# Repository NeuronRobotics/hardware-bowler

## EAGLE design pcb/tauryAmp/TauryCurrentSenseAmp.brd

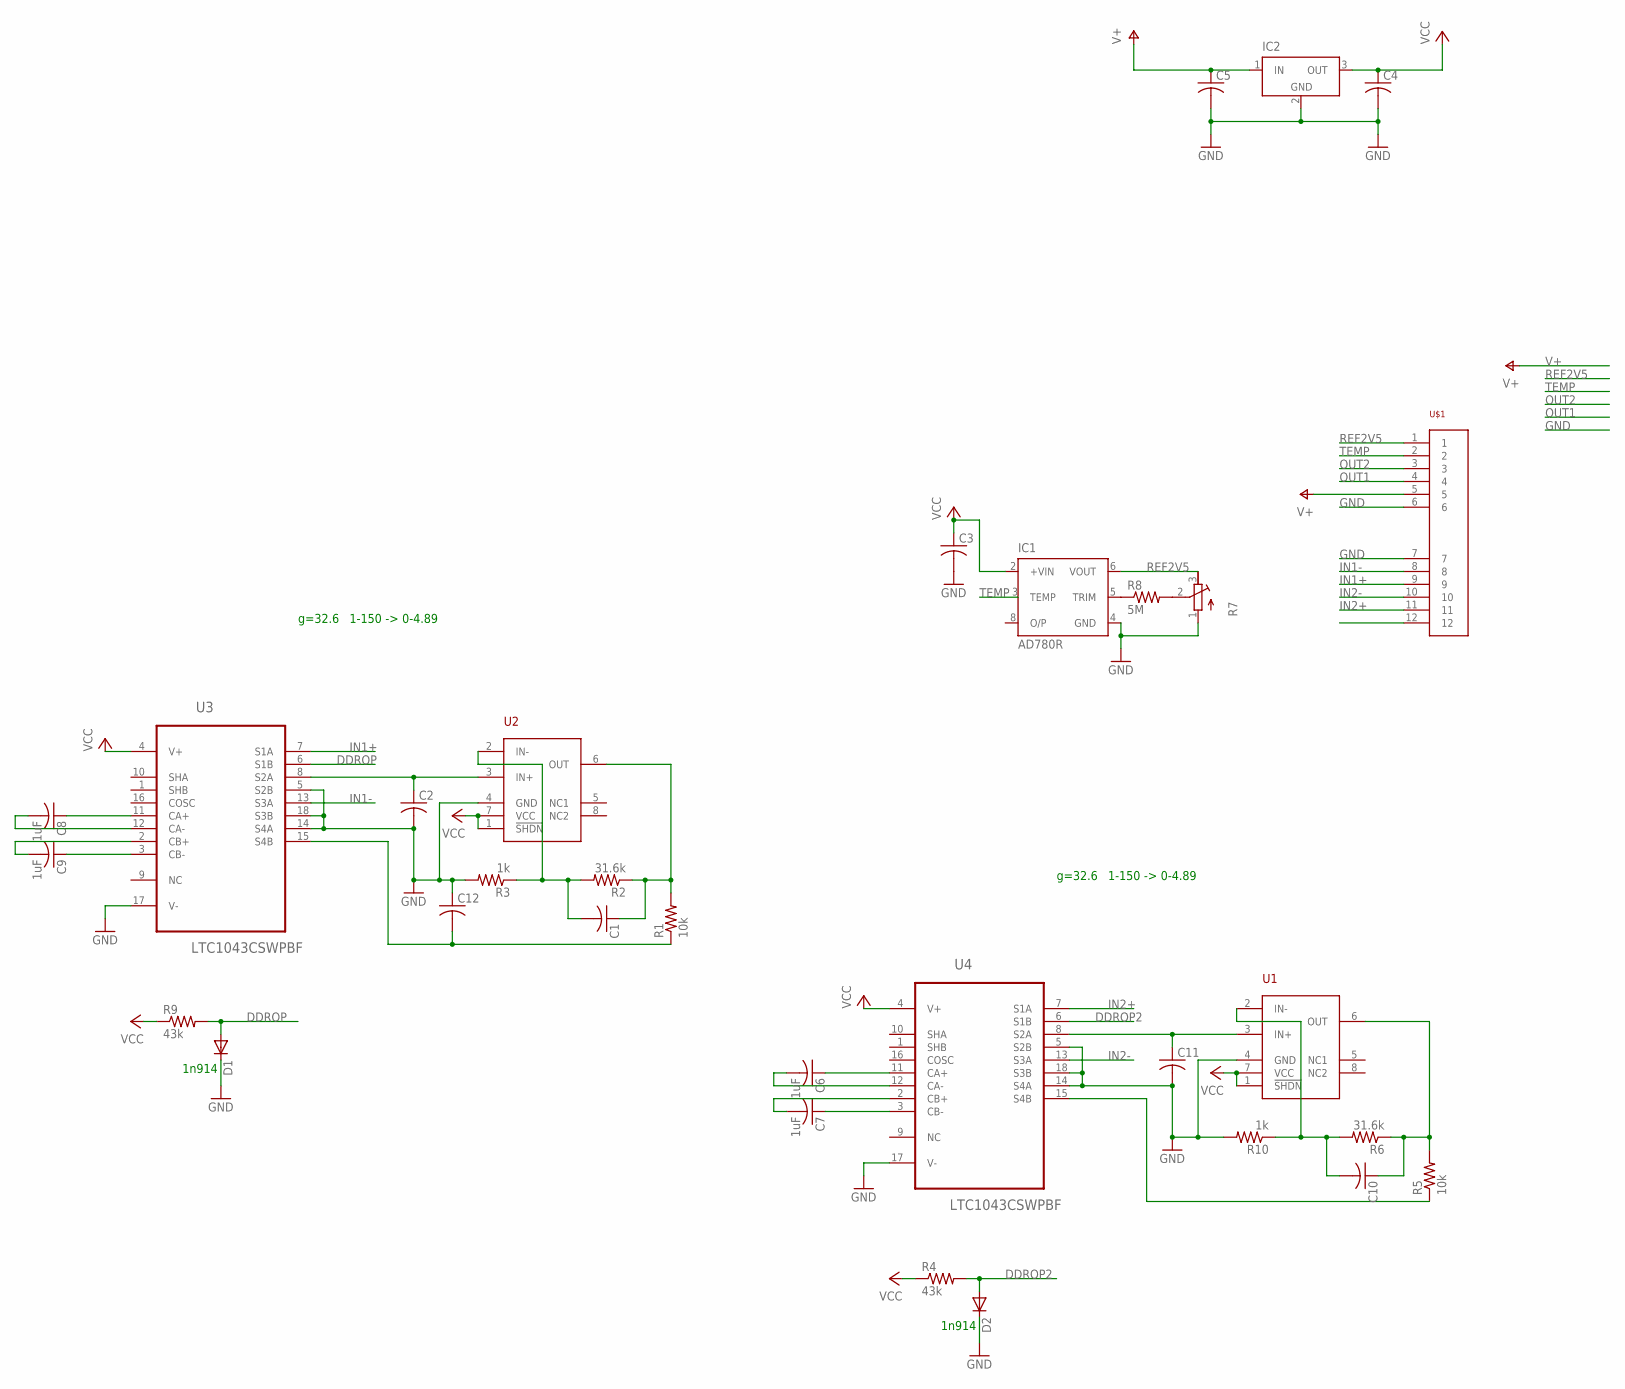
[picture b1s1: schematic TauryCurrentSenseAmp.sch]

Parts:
C1, C2, C3, C4, C5, C10, C11, C12: C-USC0805; C0805
C6, C7, C8, C9: 1uF; C0805
D1: DIODE-SOD323-R; SOD323-R
D2: DIODE-SOD523; SOD523
IC1: AD780R; SO8
IC2: LT1129CST5; SOT223
R1, R5: 10k; R0805
R2, R6: 31.6k; R0805
R3, R10: 1k; R0805
R4, R9: 43k; R0805
R7: R-TRIMM5W; RTRIM5W
R8: 5M; R0805
U1, U2: MAX4239; SO8
U3, U4: LTC1043CSWPBF; SOIC127P1032X264-18N
U$1: DMB-4770; DMB-4770-PCB

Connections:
DDROP: D1.A, R9.2, U3.6 (S1B)
DDROP2: D2.A, R4.2, U4.6 (S1B)
GND: C2.2, C3.2, C4.2, C5.2, C11.2, C12.1, D1.C, D2.C, IC1.4 (GND), IC2.2 (GND), IC2.4 (GND), R3.2, R7.1 (A), R10.2, U1.4 (GND), U2.4 (GND), U3.5 (S2B), U3.14 (S4A), U3.17 (V-), U3.18 (S3B), U4.5 (S2B), U4.14 (S4A), U4.17 (V-), U4.18 (S3B), U$1.6, U$1.7
IN1+: U3.7 (S1A), U$1.9
IN1-: U3.13 (S3A), U$1.8
IN2+: U4.7 (S1A), U$1.11
IN2-: U4.13 (S3A), U$1.10
unnamed: C2.1, U2.3 (IN+), U3.8 (S2A)
unnamed: C12.2, R1.1, U3.15 (S4B)
unnamed: C6.1, U4.11 (CA+)
unnamed: C1.2, R2.2, R3.1, U2.2 (IN-)
unnamed: IC1.5 (TRIM), R8.1
unnamed: R7.2 (S), R8.2
unnamed: C8.1, U3.11 (CA+)
unnamed: C8.2, U3.12 (CA-)
unnamed: C9.2, U3.2 (CB+)
unnamed: C9.1, U3.3 (CB-)
unnamed: C6.2, U4.12 (CA-)
unnamed: C7.2, U4.2 (CB+)
unnamed: C7.1, U4.3 (CB-)
unnamed: C11.1, U1.3 (IN+), U4.8 (S2A)
unnamed: R5.1, U4.15 (S4B)
unnamed: C10.2, R6.2, R10.1, U1.2 (IN-)
OUT1: C1.1, R1.2, R2.1, U2.6 (OUT), U$1.4
OUT2: C10.1, R5.2, R6.1, U1.6 (OUT), U$1.3
REF2V5: IC1.6 (VOUT), R7.3 (E), U$1.1
TEMP: IC1.3 (TEMP), U$1.2
V+: C5.1, IC2.1 (IN), U$1.5
VCC: C3.1, C4.1, IC1.2 (+VIN), IC2.3 (OUT), R4.1, R9.1, U1.1 (!SHDN), U1.7 (VCC), U2.1 (!SHDN), U2.7 (VCC), U3.4 (V+), U4.4 (V+)

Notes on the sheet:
1n914
g=32.6
1-150 -> 0-4.89

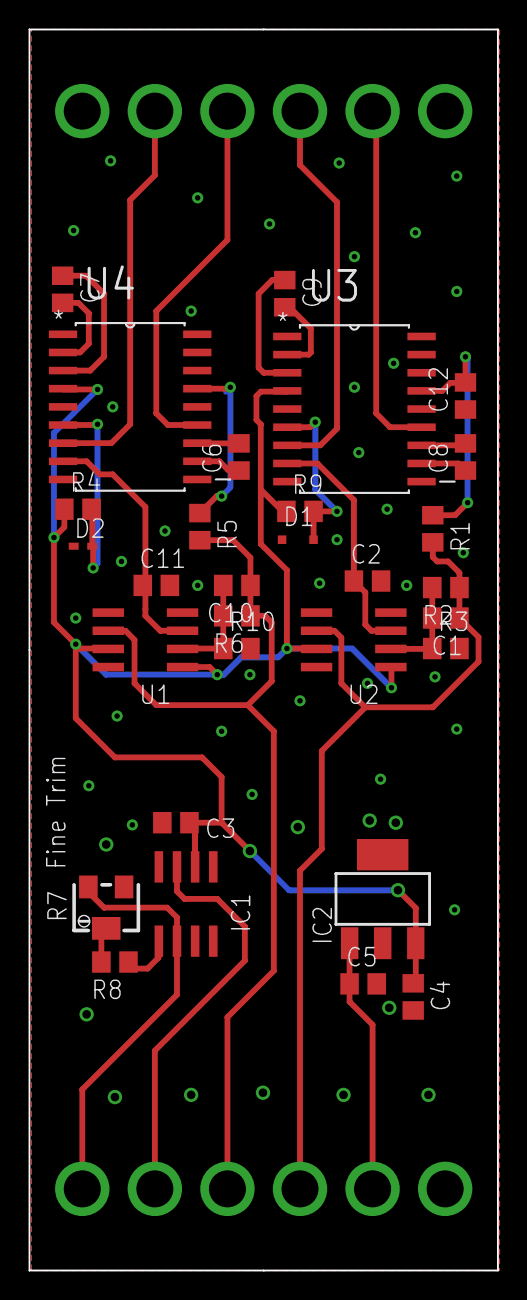
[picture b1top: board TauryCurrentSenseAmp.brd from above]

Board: 2 copper layers, 32.8 x 86.9 mm, 31 parts (0 on the bottom side), 29 nets.

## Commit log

2012-01-08 Begin 3.8.1
2012-01-20 Adding call trace to the Log
2012-01-21 Moved scheduler into NRSDK
2012-01-31 adding the link factory
2012-02-10 Tested working
2012-02-17 fix limits in hexapod
2012-03-14 All PID documented
2012-03-14 DyIO channel docs
2012-03-14 DyIO abstract peripheral comments
2012-03-22 Removed PIDChannel listener synchronization blocking
2012-03-22 Abstract timeout fix
2012-03-29 Remover unneeded prints
2012-04-12 OSX Lion working
2012-04-16 Allowing a brownout detect override
2012-04-16 DyIO detecting brownout mode for channel mode setting
2012-04-16 analog input channel link
2012-04-16 What the fcuk is up with the virtual...
2012-04-19 Virtual PID flush issue
2012-04-28 Get all channel values working
2012-05-07 another failed iterative solver
2013-05-04 =Adding all PCB source files
2013-06-24 taury amp PCB added
2013-08-22 improved analog frontend
2014-09-29 made DyIO fix boards for rev11
2014-10-03 working on testing jig, cleaned up files
2014-10-03 cleaned up dir.
2015-06-07 NEw fetfix board
